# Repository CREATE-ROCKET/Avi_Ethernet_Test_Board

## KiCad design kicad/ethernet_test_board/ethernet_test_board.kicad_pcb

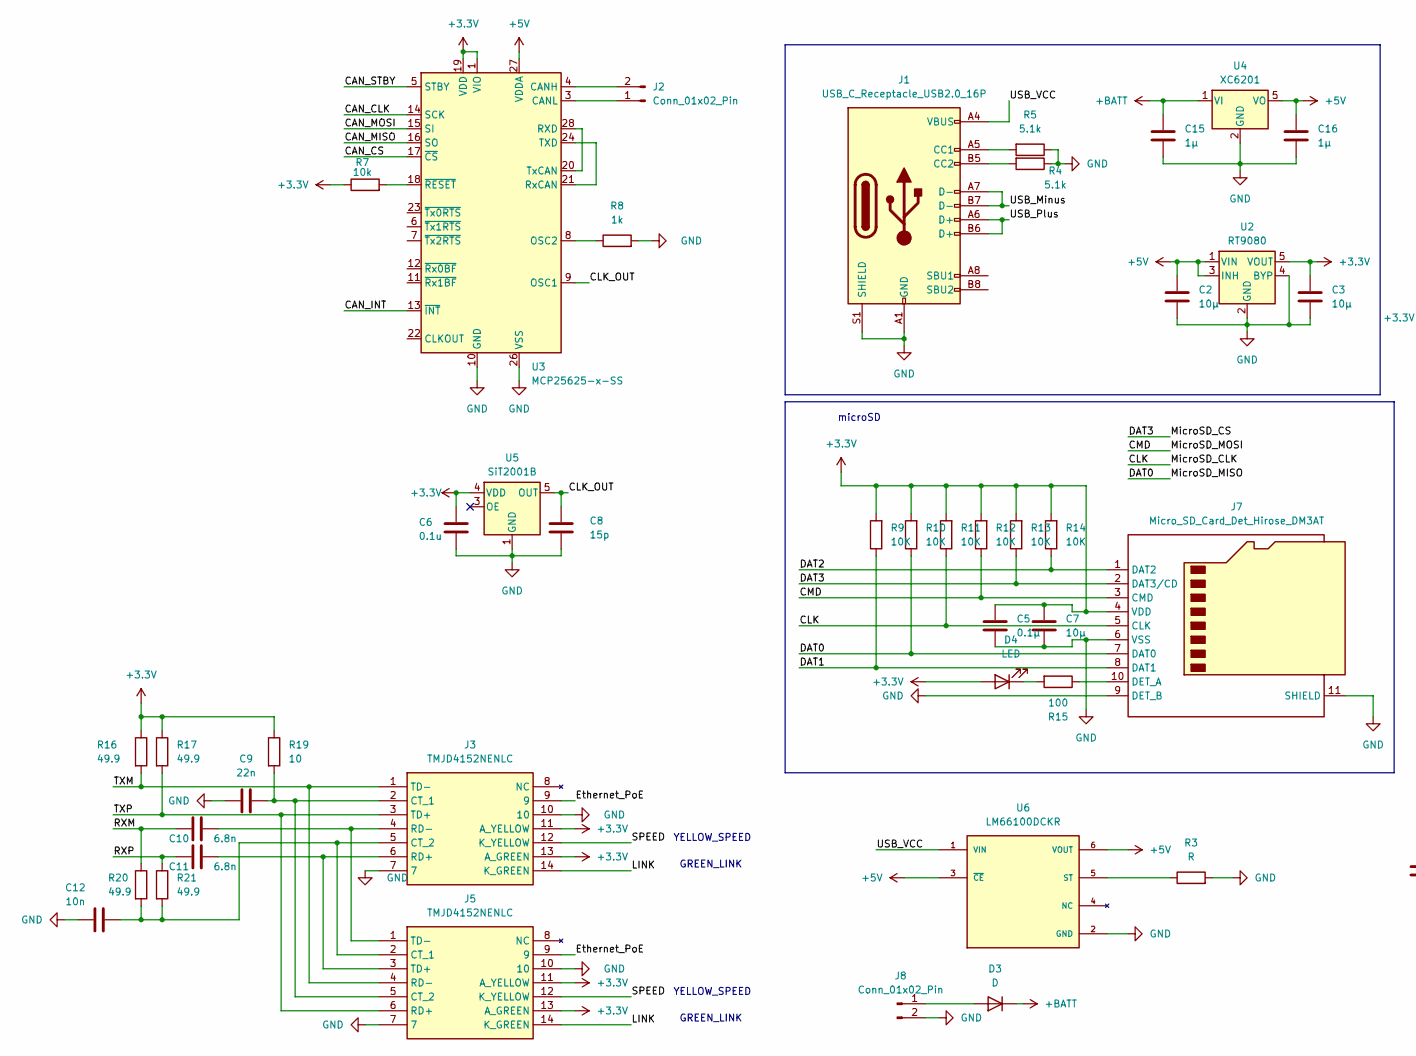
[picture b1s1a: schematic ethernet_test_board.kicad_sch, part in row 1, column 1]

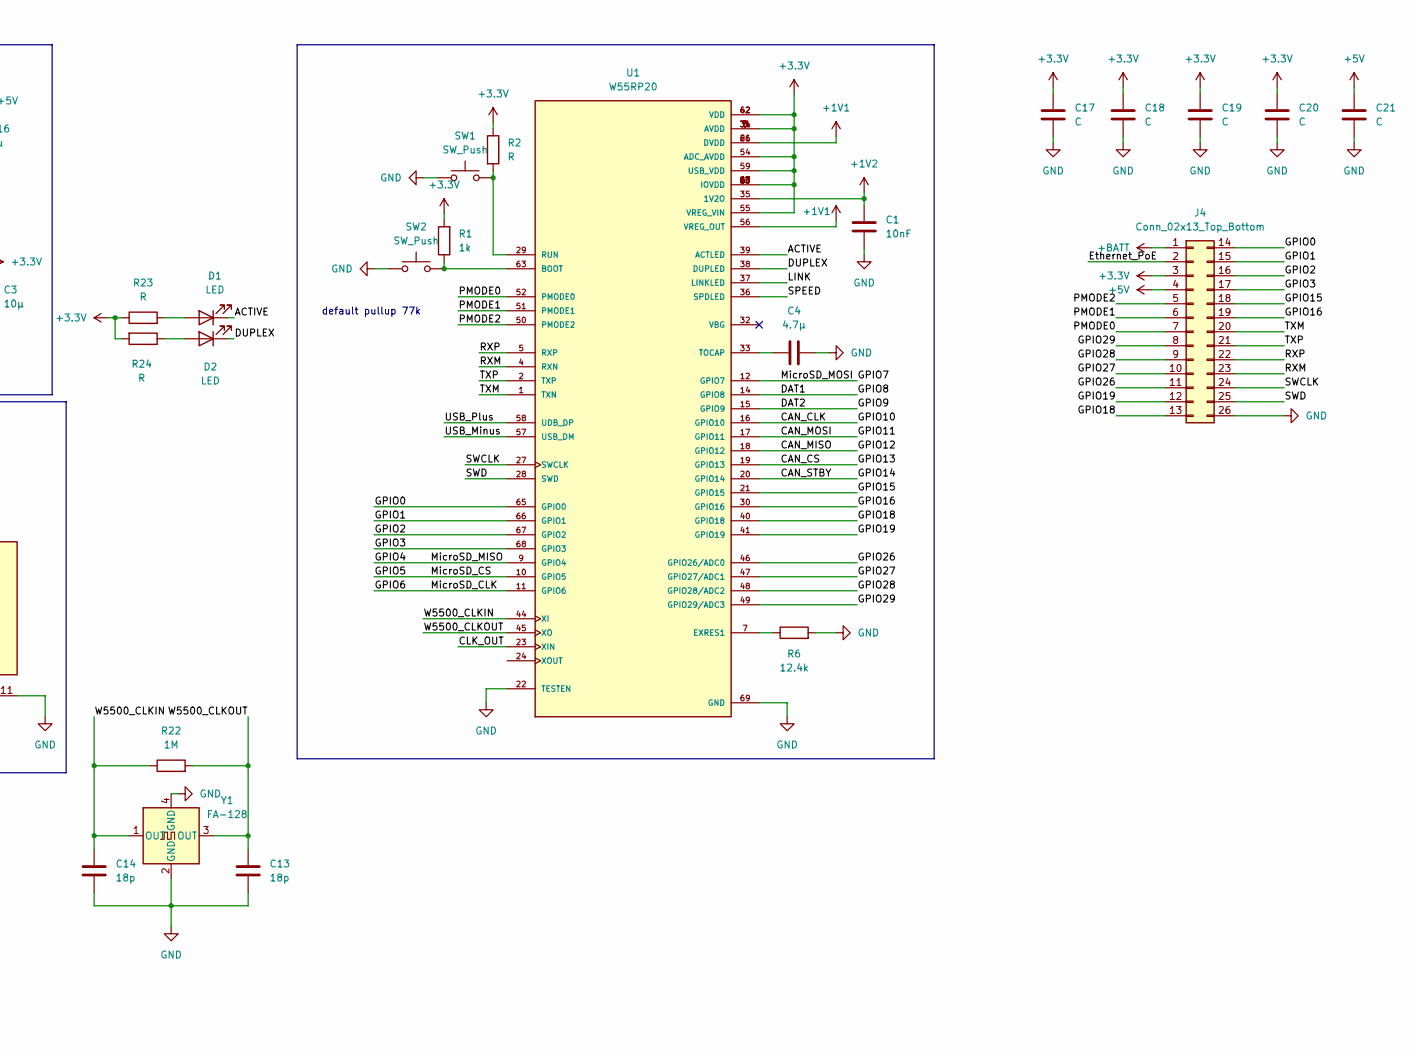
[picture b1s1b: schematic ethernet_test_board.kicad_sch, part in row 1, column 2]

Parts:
C1: 10nF; C_0603_1608Metric
C2, C3, C7: 10μ; C_0603_1608Metric
C4: 4.7μ; C_0603_1608Metric
C5: 0.1μ; C_0603_1608Metric
C6: 0.1u; C_0603_1608Metric
C8: 15p; C_0603_1608Metric
C9: 22n; C_0603_1608Metric
C10, C11: 6.8n; C_0603_1608Metric
C12: 10n; C_0603_1608Metric
C13, C14: 18p; C_0603_1608Metric
C15, C16: 1μ; C_0603_1608Metric
C17, C18, C19, C20, C21: C; C_0603_1608Metric_Pad1.08x0.95mm_HandSolder
D1, D2: LED; C_0603_1608Metric
D3: D; C_0603_1608Metric_Pad1.08x0.95mm_HandSolder
D4: LED; LED_0603_1608Metric
J1: USB_C_Receptacle_USB2.0_16P; USB_C_Receptacle_GCT_USB4105-xx-A_16P_TopMnt_Horizontal
J2: Conn_01x02_Pin; ILG2pin
J3, J5: TMJD4152NENLC; Manufacturer_Part_Number TMJD4152NENLC; Mouser Part Number 960-TMJD4152NENLC
J4: Conn_02x13_Top_Bottom; PinHeader_2x13_P2.54mm_Vertical
J7: Micro_SD_Card_Det_Hirose_DM3AT; microSD_HC_Hirose_DM3AT-SF-PEJM5
J8: Conn_01x02_Pin; JST_VH_B2P-VH-B_1x02_P3.96mm_Vertical
R1: 1k; C_0603_1608Metric
R2, R3, R23, R24: R; C_0603_1608Metric
R4, R5: 5.1k; C_0603_1608Metric
R6: 12.4k; C_0603_1608Metric
R7: 10k; R_0603_1608Metric
R8: 1k; R_0603_1608Metric
R9, R10, R11, R12, R13, R14: 10K; R_0603_1608Metric
R15: 100; R_0603_1608Metric
R16, R17, R20, R21: 49.9; C_0603_1608Metric
R19: 10; C_0603_1608Metric
R22: 1M; C_0603_1608Metric
SW1, SW2: SW_Push; SW_PUSH_6mm_H7.3mm
U1: W55RP20; QFN40P800X800X90-69N; PARTREV 0.1.0
U2: RT9080; TSOT-23-5
U3: MCP25625-x-SS; SSOP-28_5.3x10.2mm_P0.65mm
U4: XC6201; SOT-23-5
U5: SiT2001B; SOT-23-5
U6: LM66100DCKR; SOT65P210X110-6N; PARTREV Rev. A
Y1: FA-128; Oscillator_SMD_SeikoEpson_SG210-4Pin_2.5x2.0mm

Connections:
+1V1: U1.26 (DVDD), U1.56 (VREG_OUT), U1.61 (DVDD)
+1V2: C1.2, U1.35 (1V2O)
+3.3V: C3.1, C5.1, C6.1, C7.1, C17.1, C18.1, C19.1, C20.1, D4.2 (A), J3.11 (A_YELLOW), J3.13 (A_GREEN), J4.3, J5.11 (A_YELLOW), J5.13 (A_GREEN), J7.4 (VDD), R1.2, R2.1, R7.1, R9.2, R10.2, R11.2, R12.2, R13.2, R14.2, R16.1, R17.1, R19.1, R23.1, R24.2, U1.3 (AVDD), U1.6 (AVDD), U1.8 (AVDD), U1.13 (IOVDD), U1.25 (IOVDD), U1.31 (AVDD), U1.34 (AVDD), U1.42 (VDD), U1.43 (IOVDD), U1.53 (IOVDD), U1.54 (ADC_AVDD), U1.55 (VREG_VIN), U1.59 (USB_VDD), U1.60 (IOVDD), U1.62 (VDD), U1.64 (IOVDD), U2.5 (VOUT), U3.1 (VIO), U3.19 (VDD), U5.4 (VDD)
+5V: C2.1, C16.1, C21.1, J4.4, U2.1 (VIN), U2.3 (INH), U3.27 (VDDA), U4.5 (VO), U6.3 (~CE), U6.6 (VOUT)
+BATT: C15.1, D3.1 (K), J4.1, U4.1 (VI)
/ACTIVE: D1.1 (K), U1.39 (ACTLED)
/CAN_CLK: U1.16 (GPIO10), U3.14 (SCK)
/CAN_CS: U1.19 (GPIO13), U3.17 (~CS)
/CAN_INT: U3.13 (~INT)
/CAN_MISO: U1.18 (GPIO12), U3.16 (SO)
/CAN_MOSI: U1.17 (GPIO11), U3.15 (SI)
/CAN_STBY: U1.20 (GPIO14), U3.5 (STBY)
/CLK: J7.5 (CLK), R11.1, U1.11 (GPIO6)
/CLK_OUT: C8.1, U1.23 (XIN), U3.9 (OSC1), U5.5 (OUT)
/CMD: J7.3 (CMD), R12.1, U1.12 (GPIO7)
/DAT0: J7.7 (DAT0), R10.1, U1.9 (GPIO4)
/DAT1: J7.8 (DAT1), R9.1, U1.14 (GPIO8)
/DAT2: J7.1 (DAT2), R14.1, U1.15 (GPIO9)
/DAT3: J7.2 (DAT3/CD), R13.1, U1.10 (GPIO5)
/DUPLEX: D2.1 (K), U1.38 (DUPLED)
/Ethernet_PoE: J3.9, J4.2, J5.9
/GPIO0: J4.14, U1.65 (GPIO0)
/GPIO1: J4.15, U1.66 (GPIO1)
/GPIO2: J4.16, U1.67 (GPIO2)
/GPIO3: J4.17, U1.68 (GPIO3)
/GPIO15: J4.18, U1.21 (GPIO15)
/GPIO16: J4.19, U1.30 (GPIO16)
/GPIO18: J4.13, U1.40 (GPIO18)
/GPIO19: J4.12, U1.41 (GPIO19)
/GPIO26: J4.11, U1.46 (GPIO26/ADC0)
/GPIO27: J4.10, U1.47 (GPIO27/ADC1)
/GPIO28: J4.9, U1.48 (GPIO28/ADC2)
/GPIO29: J4.8, U1.49 (GPIO29/ADC3)
/LINK: J3.14 (K_GREEN), J5.14 (K_GREEN), U1.37 (LINKLED)
/PMODE0: J4.7, U1.52 (PMODE0)
/PMODE1: J4.6, U1.51 (PMODE1)
/PMODE2: J4.5, U1.50 (PMODE2)
/RXM: C10.1, J4.23, R20.1, U1.4 (RXN)
/RXP: C11.1, J4.22, R21.1, U1.5 (RXP)
/SPEED: J3.12 (K_YELLOW), J5.12 (K_YELLOW), U1.36 (SPDLED)
/SWCLK: J4.24, U1.27 (SWCLK)
/SWD: J4.25, U1.28 (SWD)
/TXM: J3.1 (TD-), J4.20, J5.4 (RD-), R16.2, U1.1 (TXN)
/TXP: J3.3 (TD+), J4.21, J5.6 (RD+), R17.2, U1.2 (TXP)
/USB_Minus: J1.A7 (D-), J1.B7 (D-), U1.57 (USB_DM)
/USB_Plus: J1.A6 (D+), J1.B6 (D+), U1.58 (UDB_DP)
/USB_VCC: J1.A4 (VBUS), J1.A9 (VBUS), J1.B4 (VBUS), J1.B9 (VBUS), U6.1 (VIN)
/W5500_CLKIN: C14.1, R22.1, U1.44 (XI), Y1.1 (OUT)
/W5500_CLKOUT: C13.1, R22.2, U1.45 (XO), Y1.3 (OUT)
GND: C1.1, C2.2, C3.2, C4.1, C5.2, C6.2, C7.2, C8.2, C9.1, C12.2, C13.2, C14.2, C15.2, C16.2, C17.2, C18.2, C19.2, C20.2, C21.2, J1.A1 (GND), J1.A12 (GND), J1.B1 (GND), J1.B12 (GND), J1.S1 (SHIELD), J3.7, J3.10, J4.26, J5.7, J5.10, J7.6 (VSS), J7.9 (DET_B), J7.11 (SHIELD), J8.2, R3.2, R4.1, R5.1, R6.2, R8.2, SW1.1, SW2.1, U1.22 (TESTEN), U1.69 (GND), U2.2 (GND), U2.4 (BYP), U3.10 (GND), U3.26 (VSS), U4.2 (GND), U5.1 (GND), U6.2 (GND), Y1.2 (GND), Y1.4 (GND)
unnamed: D1.2 (A), R23.2
unnamed: D2.2 (A), R24.1
unnamed: D3.2 (A), J8.1
unnamed: D4.1 (K), R15.2
unnamed: J1.A5 (CC1), R5.2
unnamed: J1.B5 (CC2), R4.2
unnamed: J2.1, U3.3 (CANL)
unnamed: J2.2, U3.4 (CANH)
unnamed: C9.2, J3.2 (CT_1), J5.5 (CT_2), R19.2
unnamed: C12.1, J3.5 (CT_2), J5.2 (CT_1), R20.2, R21.2
unnamed: C11.2, J3.6 (RD+), J5.3 (TD+)
unnamed: C10.2, J3.4 (RD-), J5.1 (TD-)
unnamed: J7.10 (DET_A), R15.1
unnamed: R1.1, SW2.2, U1.63 (BOOT)
unnamed: R6.1, U1.7 (EXRES1)
unnamed: R2.2, SW1.2, U1.29 (RUN)
unnamed: C4.2, U1.33 (TOCAP)
unnamed: R8.1, U3.8 (OSC2)
unnamed: U3.20 (TxCAN), U3.28 (RXD)
unnamed: U3.21 (RxCAN), U3.24 (TXD)
unnamed: R7.2, U3.18 (~RESET)
unnamed: R3.1, U6.5 (ST)

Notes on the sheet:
microSD
GREEN_LINK
YELLOW_SPEED
default pullup 77k

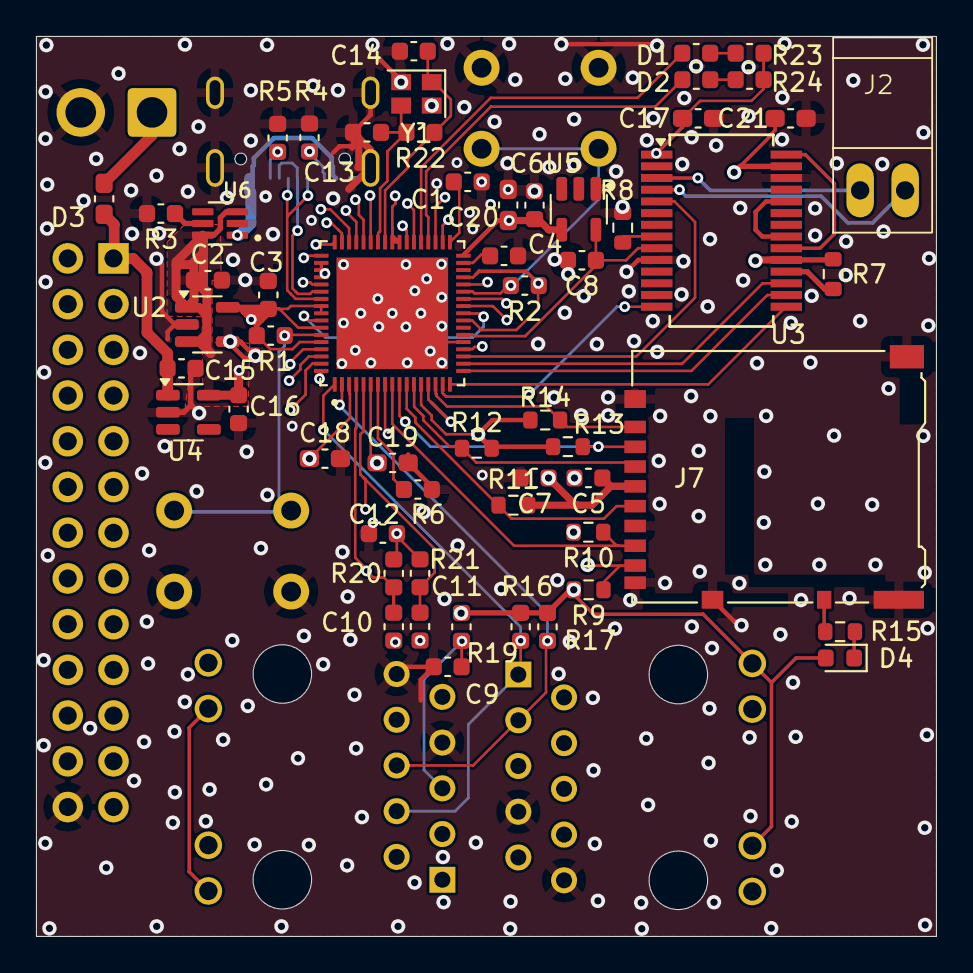
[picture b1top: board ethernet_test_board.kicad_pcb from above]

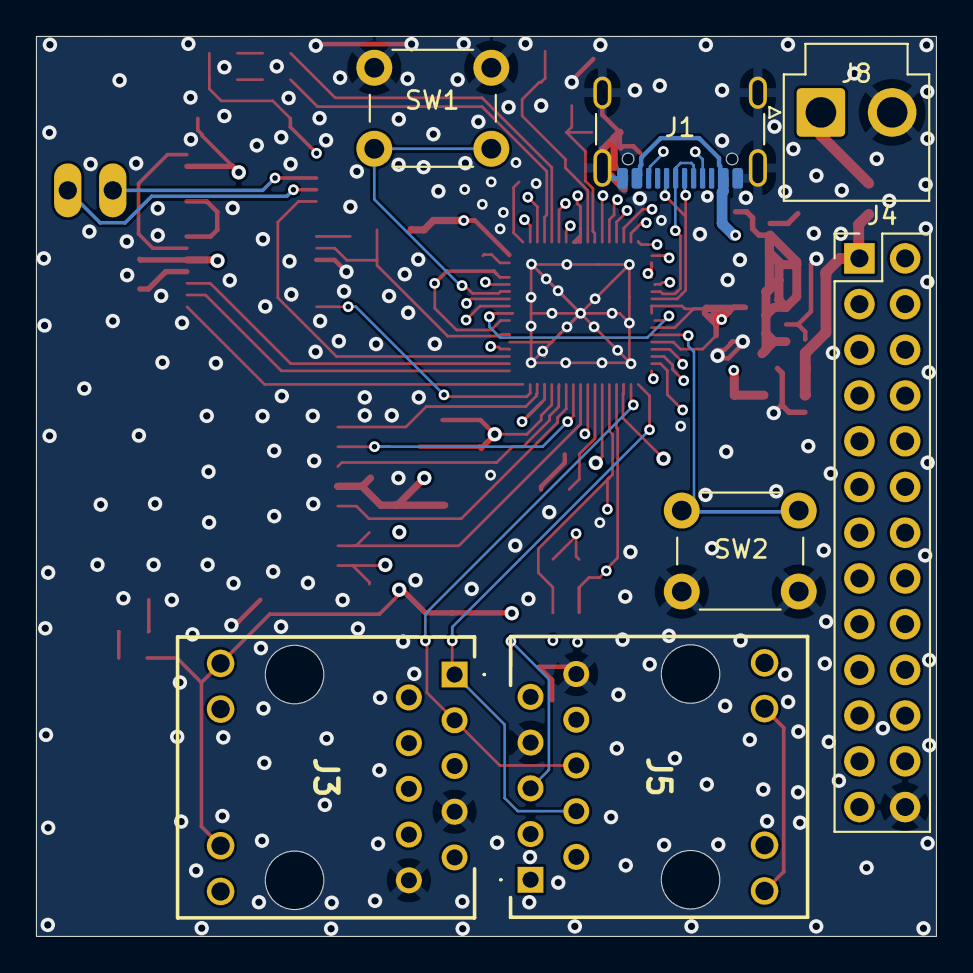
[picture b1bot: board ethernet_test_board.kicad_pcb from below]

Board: 8 copper layers, 50.0 x 50.0 mm, 64 parts (7 on the bottom side), 71 nets.

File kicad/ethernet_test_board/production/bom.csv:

Designator,Footprint,Quantity,Value,LCSC Part #
C1,0603,1,10nF,
"C10, C11",0603,2,6.8n,
C12,0603,1,10n,
"C13, C14",0603,2,18p,
"C15, C16",0603,2,1μ,
"C17, C18, C19, C20, C21",0603,5,C,
"C2, C3, C7",0603,3,10μ,
C4,0603,1,4.7μ,
C5,0603,1,0.1μ,
C6,0603,1,0.1u,
C8,0603,1,15p,
C9,0603,1,22n,
"D1, D2, D4",0603,3,LED,
D3,0603,1,D,
J1,USB_C_Receptacle_GCT_USB4105-xx-A_16P_TopMnt_Horizontal,1,USB_C_Receptacle_USB2.0_16P,
J2,ILG2pin,1,Conn_01x02_Pin,
"J3, J5",TMJD4152NENLC,2,TMJD4152NENLC,
J4,PinHeader_2x13_P2.54mm_Vertical,1,Conn_02x13_Top_Bottom,
J7,microSD_HC_Hirose_DM3AT-SF-PEJM5,1,Micro_SD_Card_Det_Hirose_DM3AT,
J8,JST_VH_B2P-VH-B_1x02_P3.96mm_Vertical,1,Conn_01x02_Pin,
"R1, R8",0603,2,1k,
"R10, R11, R12, R13, R14, R7, R9",0603,7,10K,
R15,0603,1,100,
"R16, R17, R20, R21",0603,4,49.9,
R19,0603,1,10,
"R2, R23, R24, R3",0603,4,R,
R22,0603,1,1M,
"R4, R5",0603,2,5.1k,
R6,0603,1,12.4k,
"SW1, SW2",SW_PUSH_6mm_H7.3mm,2,SW_Push,
U1,QFN40P800X800X90-69N,1,W55RP20,
U2,TSOT-23-5,1,RT9080,
U3,SSOP-28_5.3x10.2mm_P0.65mm,1,MCP25625-x-SS,
U4,SOT-23-5,1,XC6201,
U5,SOT-23-5,1,SiT2001B,
U6,SOT65P210X110-6N,1,LM66100DCKR,
Y1,Oscillator_SMD_SeikoEpson_SG210-4Pin_2.5x2.0mm,1,FA-128,

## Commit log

2025-05-02 init commit (kicad WIP)
2025-05-19 [add] kicad sch (finish) kicad pcb (WIP)
2025-06-12 [fix] kicad ethernet error
2025-07-07 [add] kicad pcb
2025-08-05 [fix] fix pcb error
2025-08-08 [fix] via size
